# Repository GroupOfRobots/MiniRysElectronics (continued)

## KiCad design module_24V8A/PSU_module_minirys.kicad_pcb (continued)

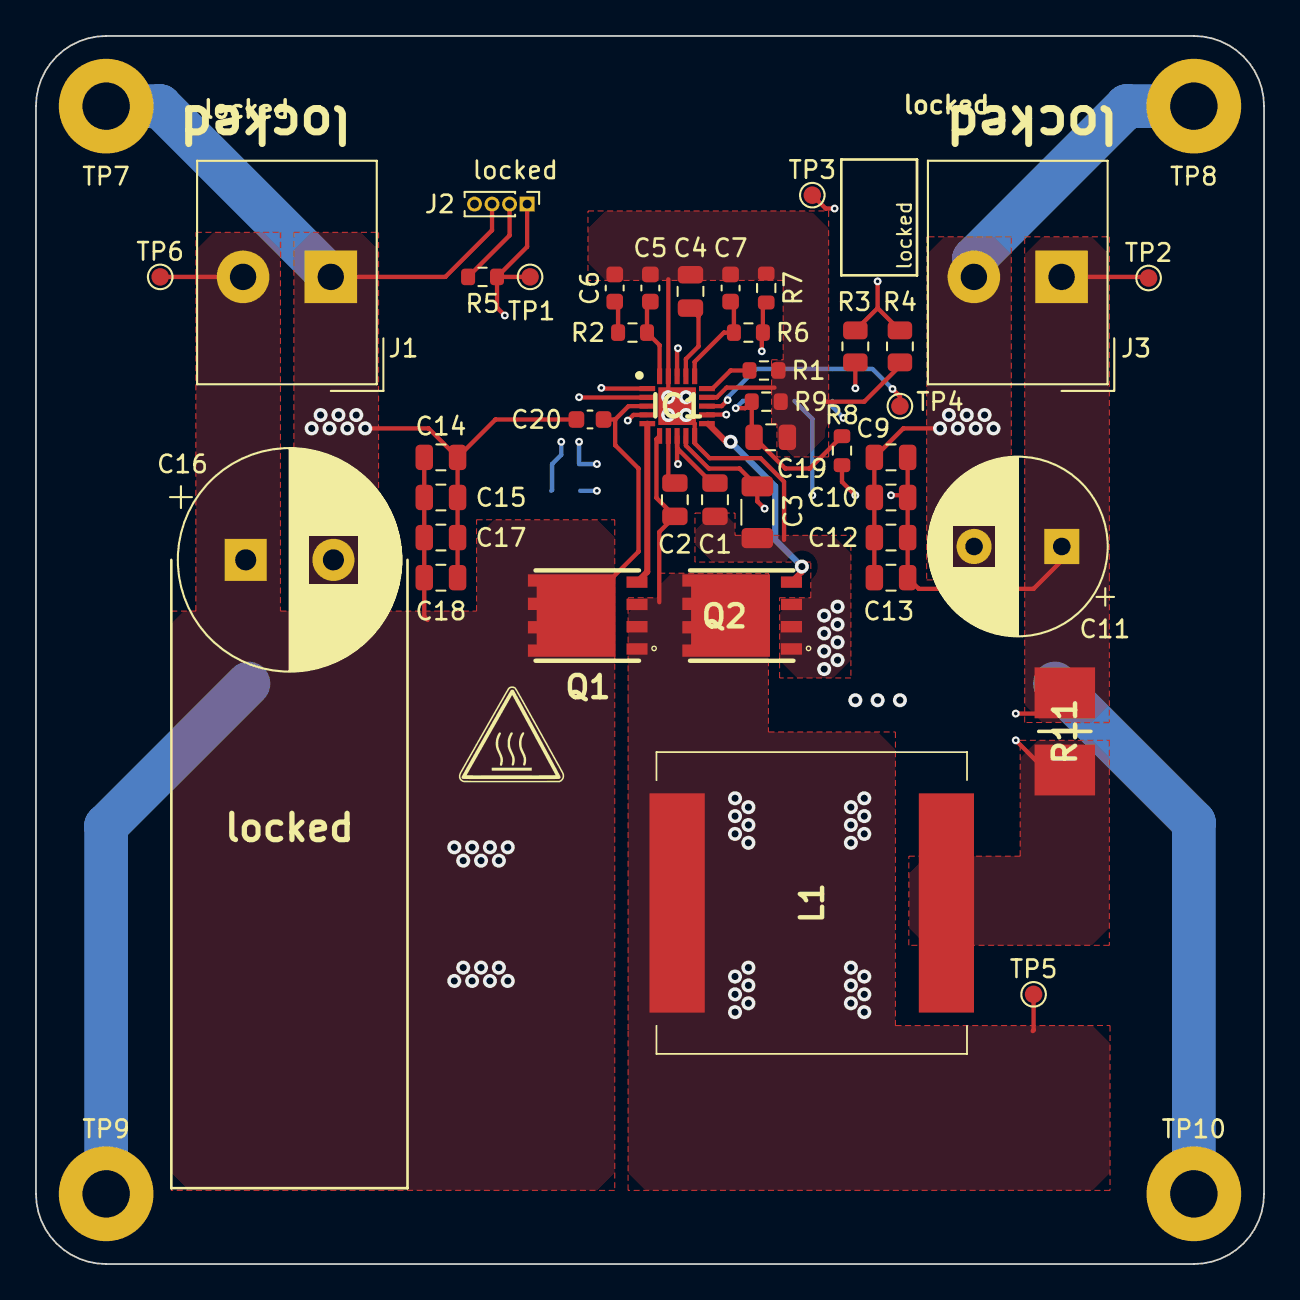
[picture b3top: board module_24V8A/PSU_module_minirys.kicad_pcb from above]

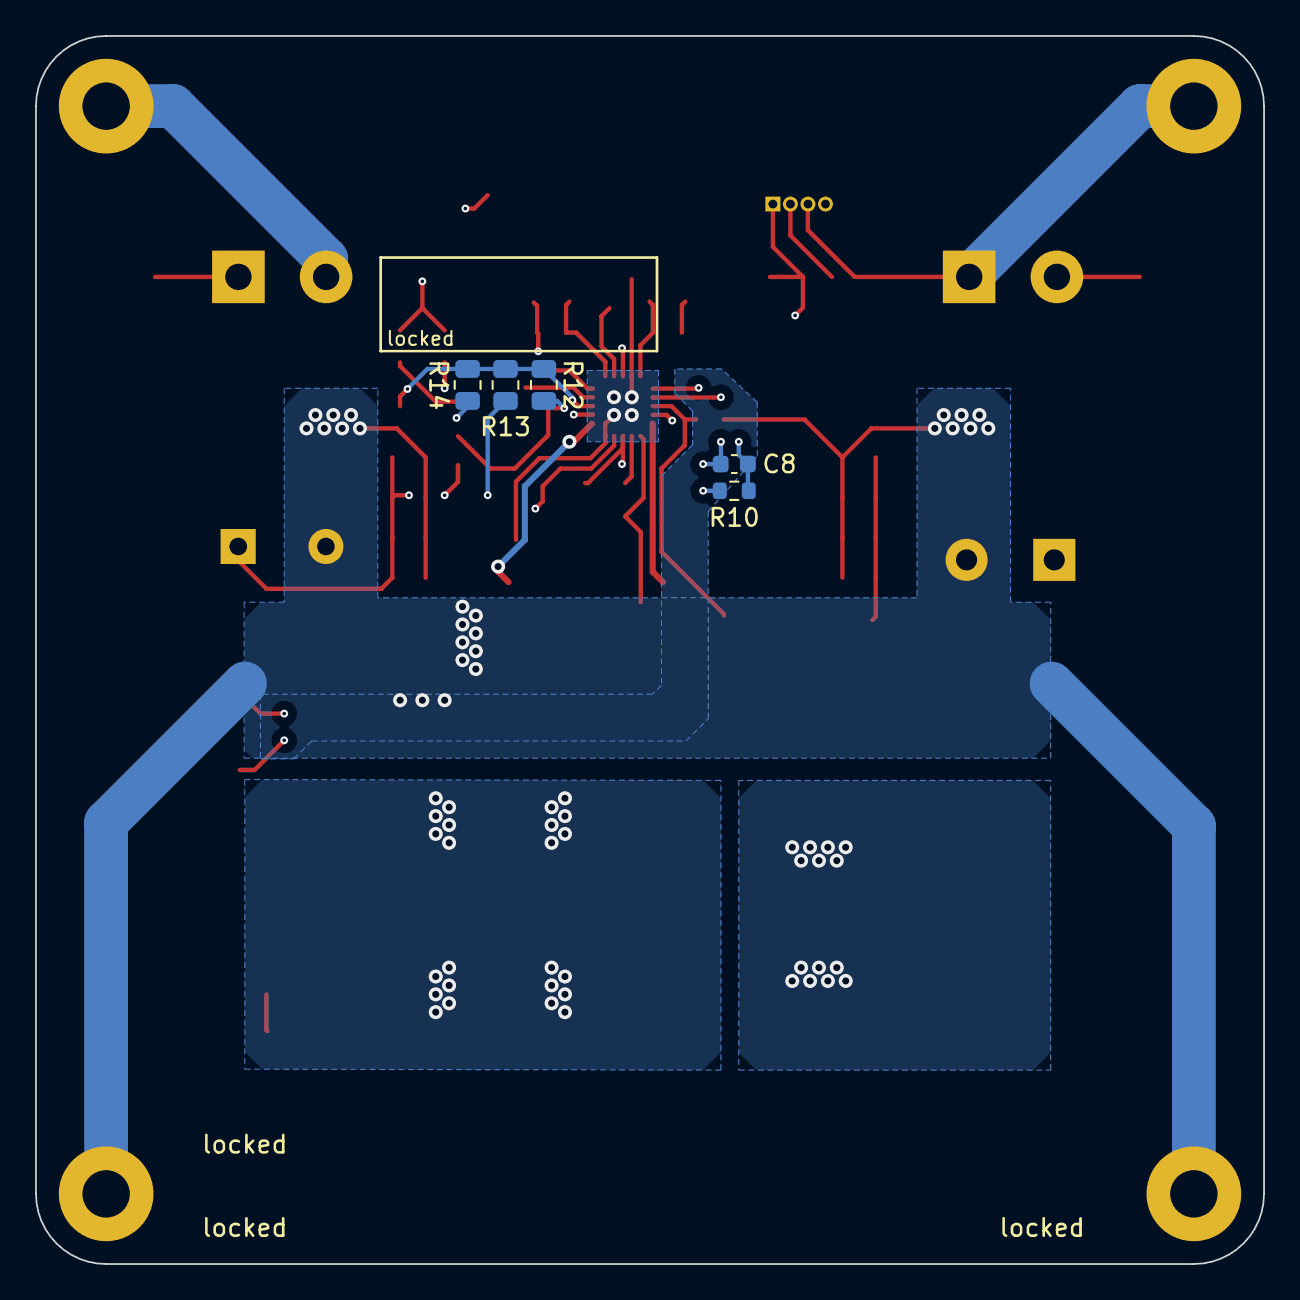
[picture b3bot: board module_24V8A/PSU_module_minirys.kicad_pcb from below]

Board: 4 copper layers, 70.0 x 70.0 mm, 51 parts (5 on the bottom side), 22 nets.

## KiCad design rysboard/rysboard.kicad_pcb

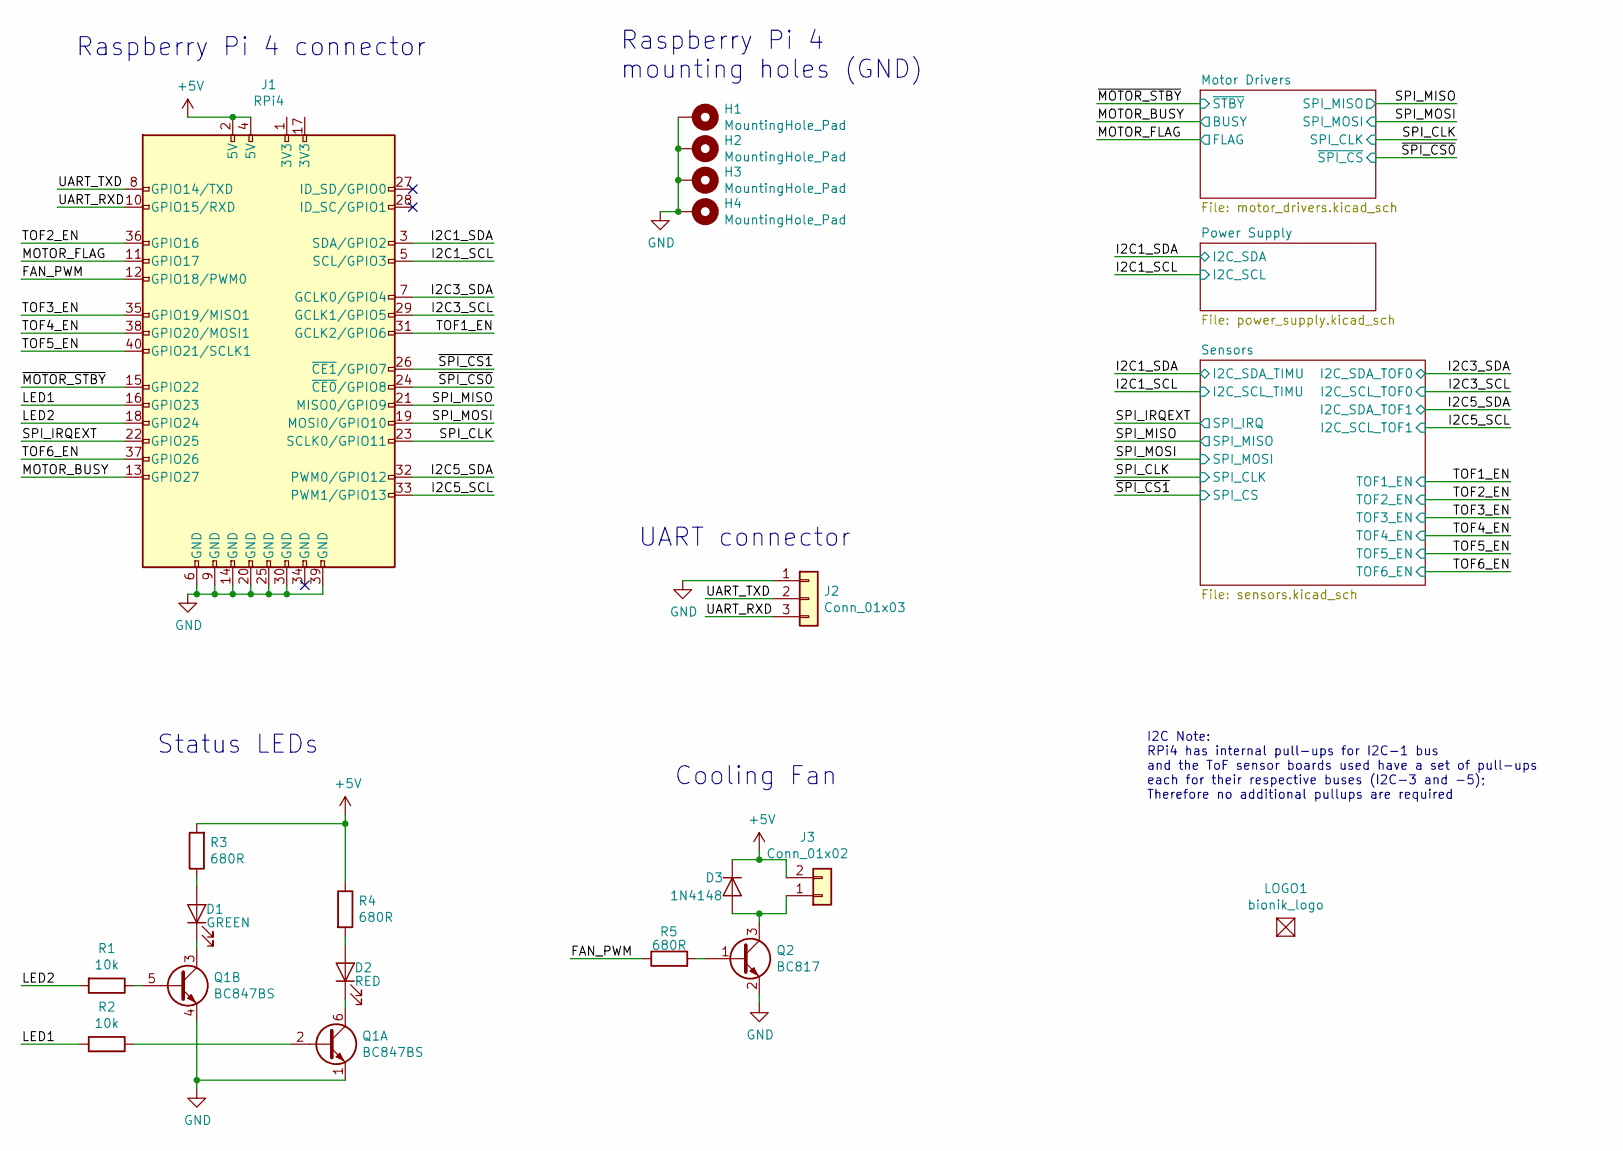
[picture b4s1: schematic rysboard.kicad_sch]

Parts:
D1: GREEN; LED_0805_2012Metric
D2: RED; LED_0805_2012Metric
D3: 1N4148; D_0603_1608Metric
H1, H2, H3, H4: MountingHole_Pad; MountingHole_2.7mm_M2.5_Pad
J1: RPi4; PinSocket_2x20_P2.54mm_Vertical
J2: Conn_01x03; PinHeader_1x03_P2.54mm_Vertical
J3: Conn_01x02; PinHeader_1x02_P2.54mm_Vertical
LOGO1: bionik_logo
Q1: BC847BS; SOT-363_SC-70-6
Q2: BC817; SOT-23
R1, R2: 10k; R_0603_1608Metric
R3, R4, R5: 680R; R_0603_1608Metric

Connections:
+5V: D3.1 (K), J1.2 (5V), J1.4 (5V), J3.2, R3.2, R4.1; also elsewhere on the board
/FAN_PWM: J1.12 (GPIO18/PWM0), R5.1
/I2C1_SCL: J1.5 (SCL/GPIO3); also elsewhere on the board
/I2C1_SDA: J1.3 (SDA/GPIO2); also elsewhere on the board
/I2C3_SCL: J1.29 (GCLK1/GPIO5); also elsewhere on the board
/I2C3_SDA: J1.7 (GCLK0/GPIO4); also elsewhere on the board
/I2C5_SCL: J1.33 (PWM1/GPIO13); also elsewhere on the board
/I2C5_SDA: J1.32 (PWM0/GPIO12); also elsewhere on the board
/LED1: J1.16 (GPIO23), R2.2
/LED2: J1.18 (GPIO24), R1.2
/MOTOR_BUSY: J1.13 (GPIO27); also elsewhere on the board
/MOTOR_FLAG: J1.11 (GPIO17); also elsewhere on the board
/SPI_CLK: J1.23 (SCLK0/GPIO11); also elsewhere on the board
/SPI_IRQEXT: J1.22 (GPIO25); also elsewhere on the board
/SPI_MISO: J1.21 (MISO0/GPIO9); also elsewhere on the board
/SPI_MOSI: J1.19 (MOSI0/GPIO10); also elsewhere on the board
/TOF1_EN: J1.31 (GCLK2/GPIO6); also elsewhere on the board
/TOF2_EN: J1.36 (GPIO16); also elsewhere on the board
/TOF3_EN: J1.35 (GPIO19/MISO1); also elsewhere on the board
/TOF4_EN: J1.38 (GPIO20/MOSI1); also elsewhere on the board
/TOF5_EN: J1.40 (GPIO21/SCLK1); also elsewhere on the board
/TOF6_EN: J1.37 (GPIO26); also elsewhere on the board
/UART_RXD: J1.10 (GPIO15/RXD), J2.3
/UART_TXD: J1.8 (GPIO14/TXD), J2.2
/~MOTOR_STBY: J1.15 (GPIO22); also elsewhere on the board
/~SPI_CS0: J1.24 (~CE0/GPIO8); also elsewhere on the board
/~SPI_CS1: J1.26 (~CE1/GPIO7); also elsewhere on the board
GND: H1.1, H2.1, H3.1, H4.1, J1.6 (GND), J1.9 (GND), J1.14 (GND), J1.20 (GND), J1.25 (GND), J1.30 (GND), J1.39 (GND), J2.1, Q1.1 (E1), Q1.4 (E2), Q2.2 (E); also elsewhere on the board
unnamed: D1.1 (K), Q1.3 (C2)
unnamed: D1.2 (A), R3.1
unnamed: D2.1 (K), Q1.6 (C1)
unnamed: D2.2 (A), R4.2
unnamed: D3.2 (A), J3.1, Q2.3 (C)
unnamed: Q1.2 (B1), R2.1
unnamed: Q1.5 (B2), R1.1
unnamed: Q2.1 (B), R5.2

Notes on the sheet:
Raspberry Pi 4 mounting holes (GND)
Cooling Fan
Status LEDs
I2C Note: RPi4 has internal pull-ups for I2C-1 bus and the ToF sensor boards used have a set of pull-ups each for their respective buses (I2C-3 and -5); Therefore no additional pullups are required
UART connector
Raspberry Pi 4 connector

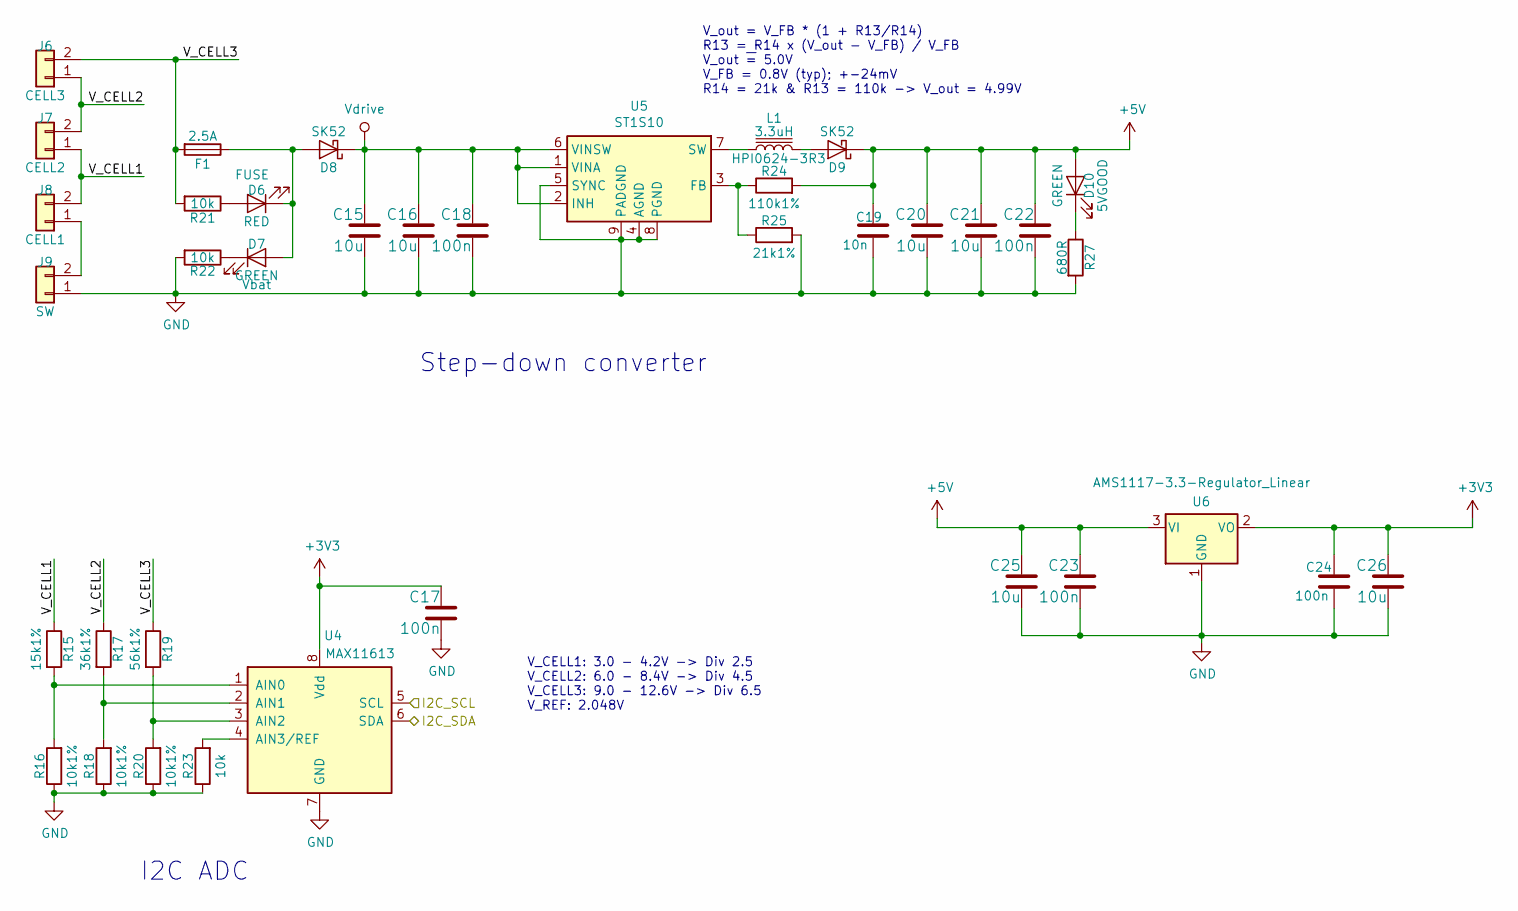
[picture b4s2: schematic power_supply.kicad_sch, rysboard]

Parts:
C15, C16, C20, C21: 10u; C_1206_3216Metric
C17, C18, C22, C23, C24: 100n; C_0603_1608Metric
C19: 10n; C_0603_1608Metric
C25, C26: 10u; C_0603_1608Metric
D6: RED; LED_0805_2012Metric
D7, D10: GREEN; LED_0805_2012Metric
D8, D9: SK52; D_SMB
F1: 2.5A; Fuse_1206_3216Metric
J6: CELL3; Molex_Micro-Fit_3.0_43045-0212_2x01_P3.00mm_Vertical
J7: CELL2; Molex_Micro-Fit_3.0_43045-0212_2x01_P3.00mm_Vertical
J8: CELL1; Molex_Micro-Fit_3.0_43045-0212_2x01_P3.00mm_Vertical
J9: SW; Molex_Micro-Fit_3.0_43045-0212_2x01_P3.00mm_Vertical
L1: 3.3uH; L_6.7x6.7_H2.2
R15: 15k1%; R_0603_1608Metric
R16, R18, R20: 10k1%; R_0603_1608Metric
R17: 36k1%; R_0603_1608Metric
R19: 56k1%; R_0603_1608Metric
R21, R22, R23: 10k; R_0603_1608Metric
R24: 110k1%; R_0603_1608Metric
R25: 21k1%; R_0603_1608Metric
R27: 680R; R_0603_1608Metric
U4: MAX11613; 8-uMAX; PartID MAX11613EUA+
U5: ST1S10; TI_SO-PowerPAD-8; PartID ST1S10PHR
U6: AMS1117-3.3-Regulator_Linear; SOT-223_New

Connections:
+3V3: C17.1, C24.1, C26.1, U4.8 (Vdd), U6.2 (VO); also elsewhere on the board
+5V: C19.1, C20.1, C21.1, C22.1, C23.1, C25.1, D9.1 (K), D10.2 (A), R24.2, U6.3 (VI); also elsewhere on the board
/I2C1_SCL: U4.5 (SCL); also elsewhere on the board
/I2C1_SDA: U4.6 (SDA); also elsewhere on the board
/Power Supply/V_CELL1: J7.1, J8.2, R15.1
/Power Supply/V_CELL2: J6.1, J7.2, R17.1
/Power Supply/V_CELL3: F1.2, J6.2, R19.1, R21.2
GND: C15.2, C16.2, C17.2, C18.2, C19.2, C20.2, C21.2, C22.2, C23.2, C24.2, C25.2, C26.2, J9.1, R16.1, R18.1, R20.1, R22.2, R23.1, R25.2, R27.2, U4.7 (GND), U5.4 (AGND), U5.5 (SYNC), U5.8 (PGND), U5.9 (PADGND), U6.1 (GND); also elsewhere on the board
unnamed: D6.1 (K), D7.2 (A), D8.2 (A), F1.1
unnamed: D6.2 (A), R21.1
unnamed: D7.1 (K), R22.1
unnamed: D9.2 (A), L1.2
unnamed: D10.1 (K), R27.1
unnamed: J8.1, J9.2
unnamed: L1.1, U5.7 (SW)
unnamed: R15.2, R16.2, U4.1 (AIN0)
unnamed: R17.2, R18.2, U4.2 (AIN1)
unnamed: R19.2, R20.2, U4.3 (AIN2)
unnamed: R23.2, U4.4 (AIN3/REF)
unnamed: R24.1, R25.1, U5.3 (FB)
Vdrive: C15.1, C16.1, C18.1, D8.1 (K), U5.1 (VINA), U5.2 (INH), U5.6 (VINSW); also elsewhere on the board

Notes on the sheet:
Step-down converter
V_out = V_FB * (1 + R13/R14) R13 = R14 x (V_out - V_FB) / V_FB V_out ~{=} 5.0V V_FB = 0.8V (typ); +-24mV R14 = 21k & R13 = 110k -> V_out = 4.99V
V_CELL1: 3.0 - 4.2V -> Div 2.5 V_CELL2: 6.0 - 8.4V -> Div 4.5 V_CELL3: 9.0 - 12.6V -> Div 6.5 V_REF: 2.048V
I2C ADC

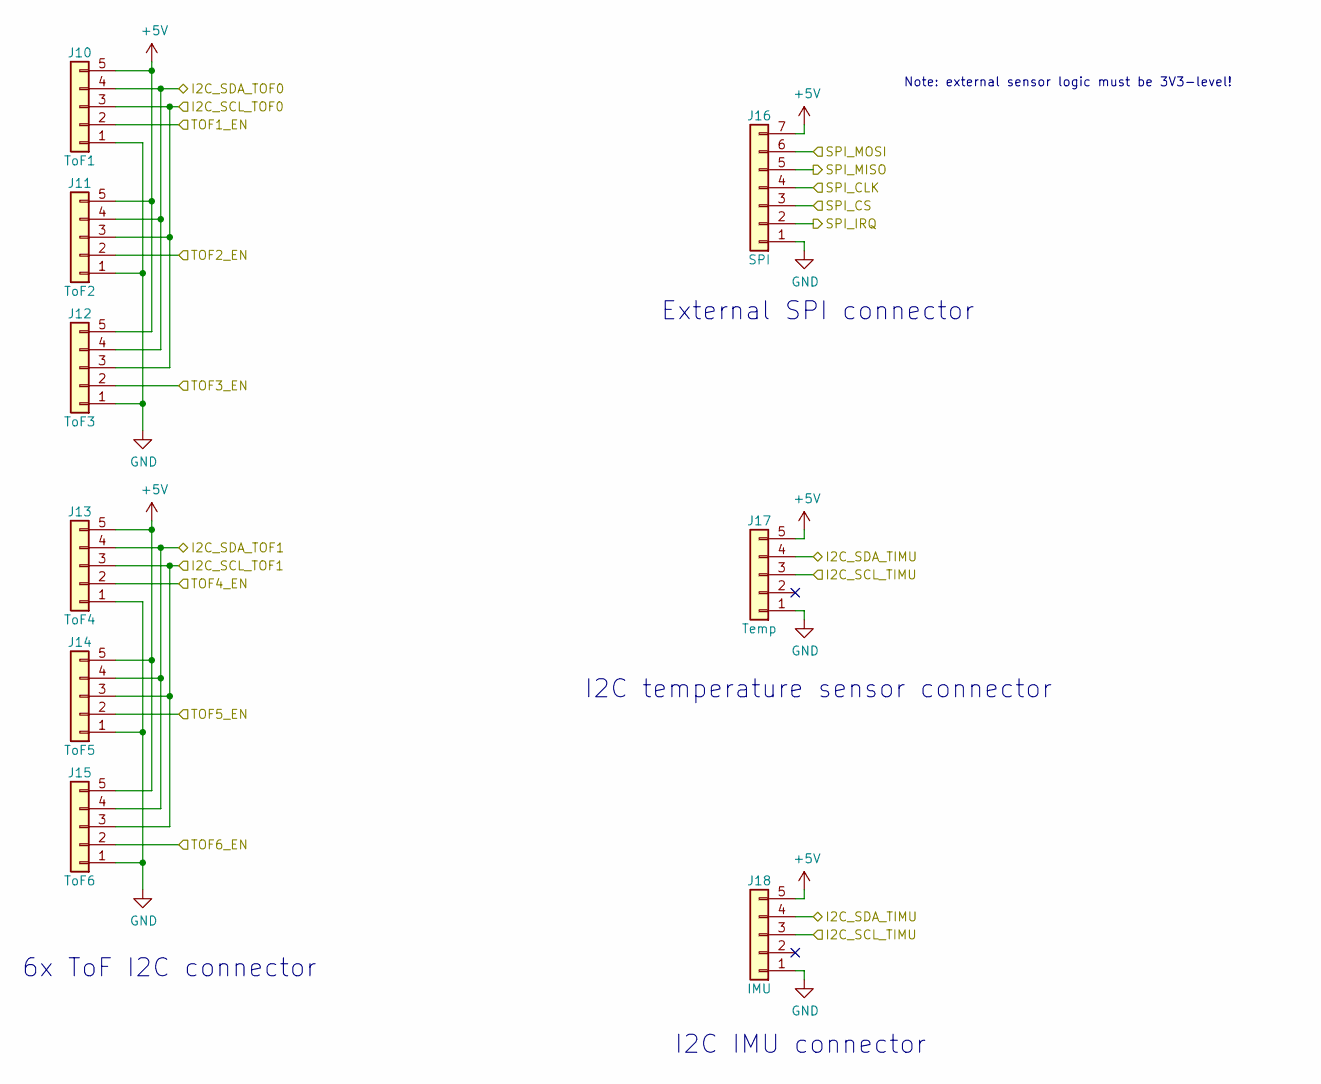
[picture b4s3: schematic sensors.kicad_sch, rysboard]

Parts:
J10: ToF1; Molex_PicoBlade_53047-0510_1x05_P1.25mm_Vertical
J11: ToF2; Molex_PicoBlade_53047-0510_1x05_P1.25mm_Vertical
J12: ToF3; Molex_PicoBlade_53047-0510_1x05_P1.25mm_Vertical
J13: ToF4; Molex_PicoBlade_53047-0510_1x05_P1.25mm_Vertical
J14: ToF5; Molex_PicoBlade_53047-0510_1x05_P1.25mm_Vertical
J15: ToF6; Molex_PicoBlade_53047-0510_1x05_P1.25mm_Vertical
J16: SPI; Molex_PicoBlade_53047-0710_1x07_P1.25mm_Vertical
J17: Temp; Molex_PicoBlade_53047-0510_1x05_P1.25mm_Vertical
J18: IMU; Molex_PicoBlade_53047-0510_1x05_P1.25mm_Vertical

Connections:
+5V: J10.5, J11.5, J12.5, J13.5, J14.5, J15.5, J16.7, J17.5, J18.5; also elsewhere on the board
/I2C1_SCL: J17.3, J18.3; also elsewhere on the board
/I2C1_SDA: J17.4, J18.4; also elsewhere on the board
/I2C3_SCL: J10.3, J11.3, J12.3; also elsewhere on the board
/I2C3_SDA: J10.4, J11.4, J12.4; also elsewhere on the board
/I2C5_SCL: J13.3, J14.3, J15.3; also elsewhere on the board
/I2C5_SDA: J13.4, J14.4, J15.4; also elsewhere on the board
/SPI_CLK: J16.4; also elsewhere on the board
/SPI_IRQEXT: J16.2; also elsewhere on the board
/SPI_MISO: J16.5; also elsewhere on the board
/SPI_MOSI: J16.6; also elsewhere on the board
/TOF1_EN: J10.2; also elsewhere on the board
/TOF2_EN: J11.2; also elsewhere on the board
/TOF3_EN: J12.2; also elsewhere on the board
/TOF4_EN: J13.2; also elsewhere on the board
/TOF5_EN: J14.2; also elsewhere on the board
/TOF6_EN: J15.2; also elsewhere on the board
/~SPI_CS1: J16.3; also elsewhere on the board
GND: J10.1, J11.1, J12.1, J13.1, J14.1, J15.1, J16.1, J17.1, J18.1; also elsewhere on the board

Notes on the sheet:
Note: external sensor logic must be 3V3-level!
External SPI connector
I2C temperature sensor connector
I2C IMU connector
6x ToF I2C connector

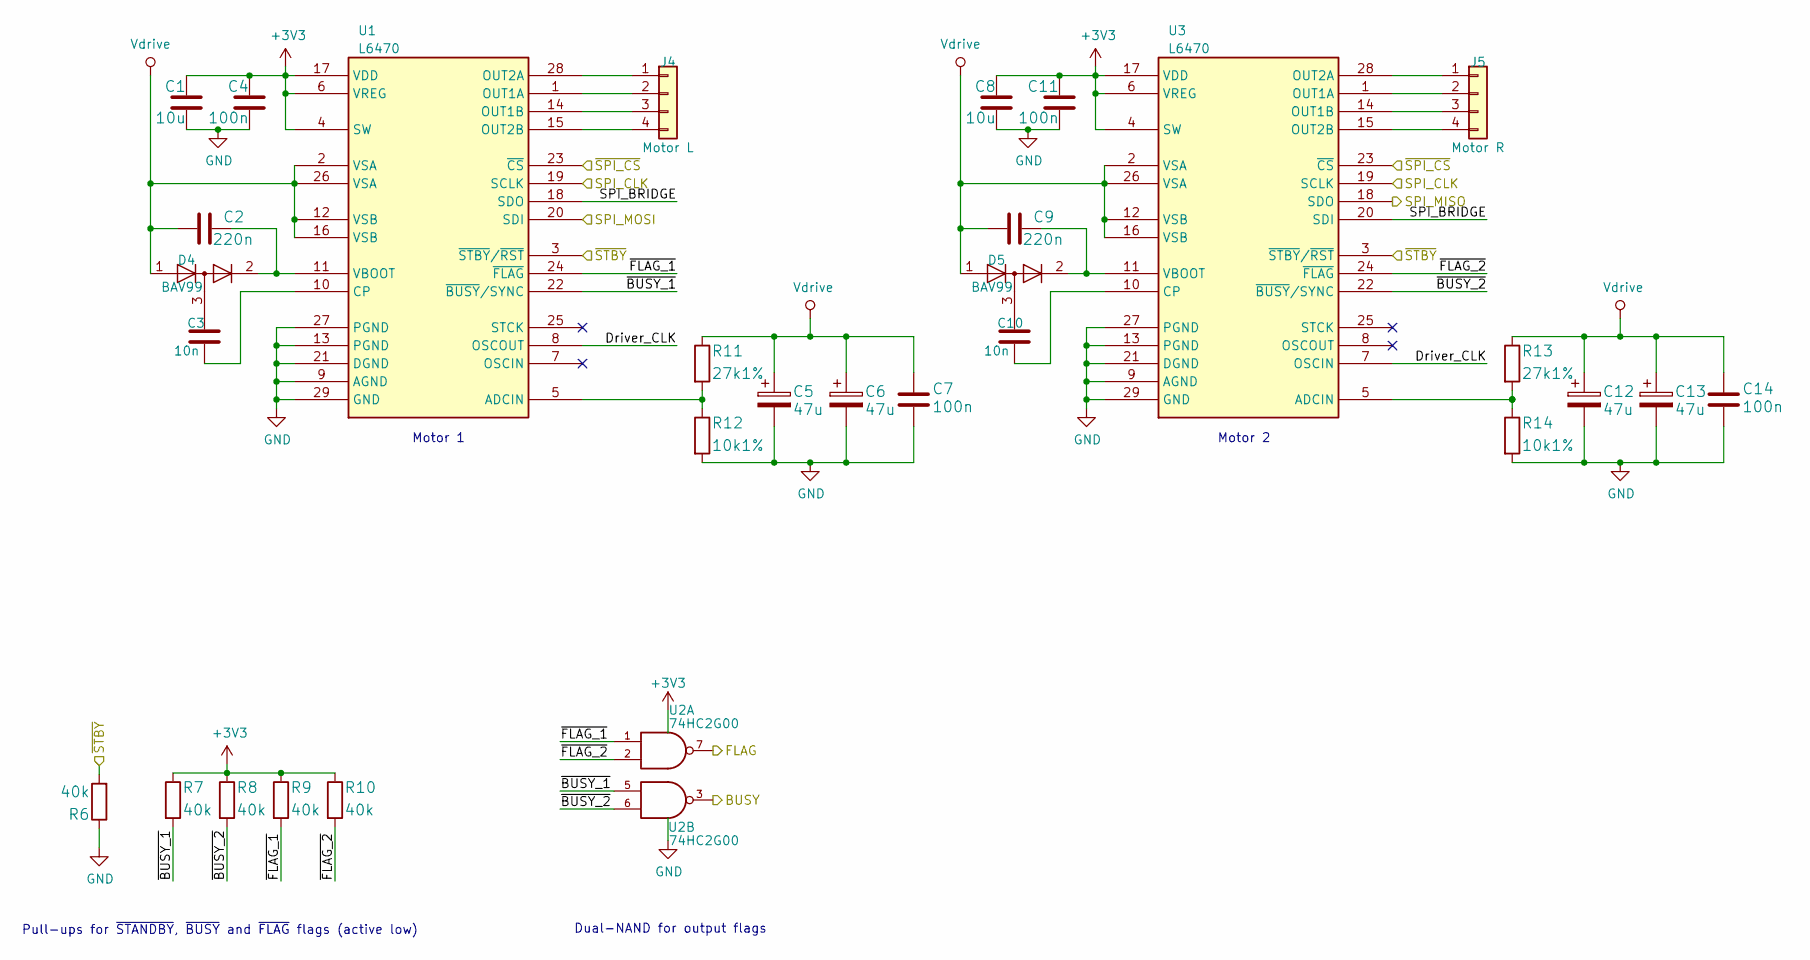
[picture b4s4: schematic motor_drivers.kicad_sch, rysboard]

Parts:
C1, C8: 10u; C_1206_3216Metric
C2, C9: 220n; C_0805_2012Metric
C3, C10: 10n; C_0603_1608Metric
C4, C7, C11, C14: 100n; C_0603_1608Metric
C5, C6, C12, C13: 47u; CP_EIA-7343-31_Kemet-D
D4, D5: BAV99; SOT-23
J4: Motor L; Molex_Micro-Fit_3.0_43650-0415_1x04_P3.00mm_Vertical
J5: Motor R; Molex_Micro-Fit_3.0_43650-0415_1x04_P3.00mm_Vertical
R6, R7, R8, R9, R10: 40k; R_0603_1608Metric
R11, R13: 27k1%; R_0603_1608Metric
R12, R14: 10k1%; R_0603_1608Metric
U1, U3: L6470; HTSSOP-28-1EP_4.4x9.7mm_P0.65mm_EP3.4x9.5mm_ThermalVias; PartID L6470H
U2: 74HC2G00; TSSOP-8_3x3mm_P0.65mm

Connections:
+3V3: C1.1, C4.1, C8.1, C11.1, R7.1, R8.1, R9.1, R10.1, U1.4 (SW), U1.6 (VREG), U1.17 (VDD), U2.8 (VCC), U3.4 (SW), U3.6 (VREG), U3.17 (VDD); also elsewhere on the board
/MOTOR_BUSY: U2.3; also elsewhere on the board
/MOTOR_FLAG: U2.7; also elsewhere on the board
/Motor Drivers/Driver_CLK: U1.8 (OSCOUT), U3.7 (OSCIN)
/Motor Drivers/SPI_BRIDGE: U1.18 (SDO), U3.20 (SDI)
/Motor Drivers/~BUSY_1: R7.2, U1.22 (~BUSY/SYNC), U2.5
/Motor Drivers/~BUSY_2: R8.2, U2.6, U3.22 (~BUSY/SYNC)
/Motor Drivers/~FLAG_1: R9.2, U1.24 (~FLAG), U2.1
/Motor Drivers/~FLAG_2: R10.2, U2.2, U3.24 (~FLAG)
/SPI_CLK: U1.19 (SCLK), U3.19 (SCLK); also elsewhere on the board
/SPI_MISO: U3.18 (SDO); also elsewhere on the board
/SPI_MOSI: U1.20 (SDI); also elsewhere on the board
/~MOTOR_STBY: R6.2, U1.3 (~STBY/~RST), U3.3 (~STBY/~RST); also elsewhere on the board
/~SPI_CS0: U1.23 (~CS), U3.23 (~CS); also elsewhere on the board
GND: C1.2, C4.2, C5.2, C6.2, C7.2, C8.2, C11.2, C12.2, C13.2, C14.2, R6.1, R12.2, R14.2, U1.9 (AGND), U1.13 (PGND), U1.21 (DGND), U1.27 (PGND), U1.29 (GND), U2.4 (GND), U3.9 (AGND), U3.13 (PGND), U3.21 (DGND), U3.27 (PGND), U3.29 (GND); also elsewhere on the board
unnamed: C2.2, D4.2 (A), U1.11 (VBOOT)
unnamed: C3.1, D4.3 (K)
unnamed: C3.2, U1.10 (CP)
unnamed: C9.2, D5.2 (A), U3.11 (VBOOT)
unnamed: C10.1, D5.3 (K)
unnamed: C10.2, U3.10 (CP)
unnamed: J4.1, U1.28 (OUT2A)
unnamed: J4.2, U1.1 (OUT1A)
unnamed: J4.3, U1.14 (OUT1B)
unnamed: J4.4, U1.15 (OUT2B)
unnamed: J5.1, U3.28 (OUT2A)
unnamed: J5.2, U3.1 (OUT1A)
unnamed: J5.3, U3.14 (OUT1B)
unnamed: J5.4, U3.15 (OUT2B)
unnamed: R11.2, R12.1, U1.5 (ADCIN)
unnamed: R13.2, R14.1, U3.5 (ADCIN)
Vdrive: C2.1, C5.1, C6.1, C7.1, C9.1, C12.1, C13.1, C14.1, D4.1 (K), D5.1 (K), R11.1, R13.1, U1.2 (VSA), U1.12 (VSB), U1.16 (VSB), U1.26 (VSA), U3.2 (VSA), U3.12 (VSB), U3.16 (VSB), U3.26 (VSA); also elsewhere on the board

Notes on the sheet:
Motor 1
Motor 2
Pull-ups for ~{STANDBY}, ~{BUSY} and ~{FLAG} flags (active low)
Dual-NAND for output flags

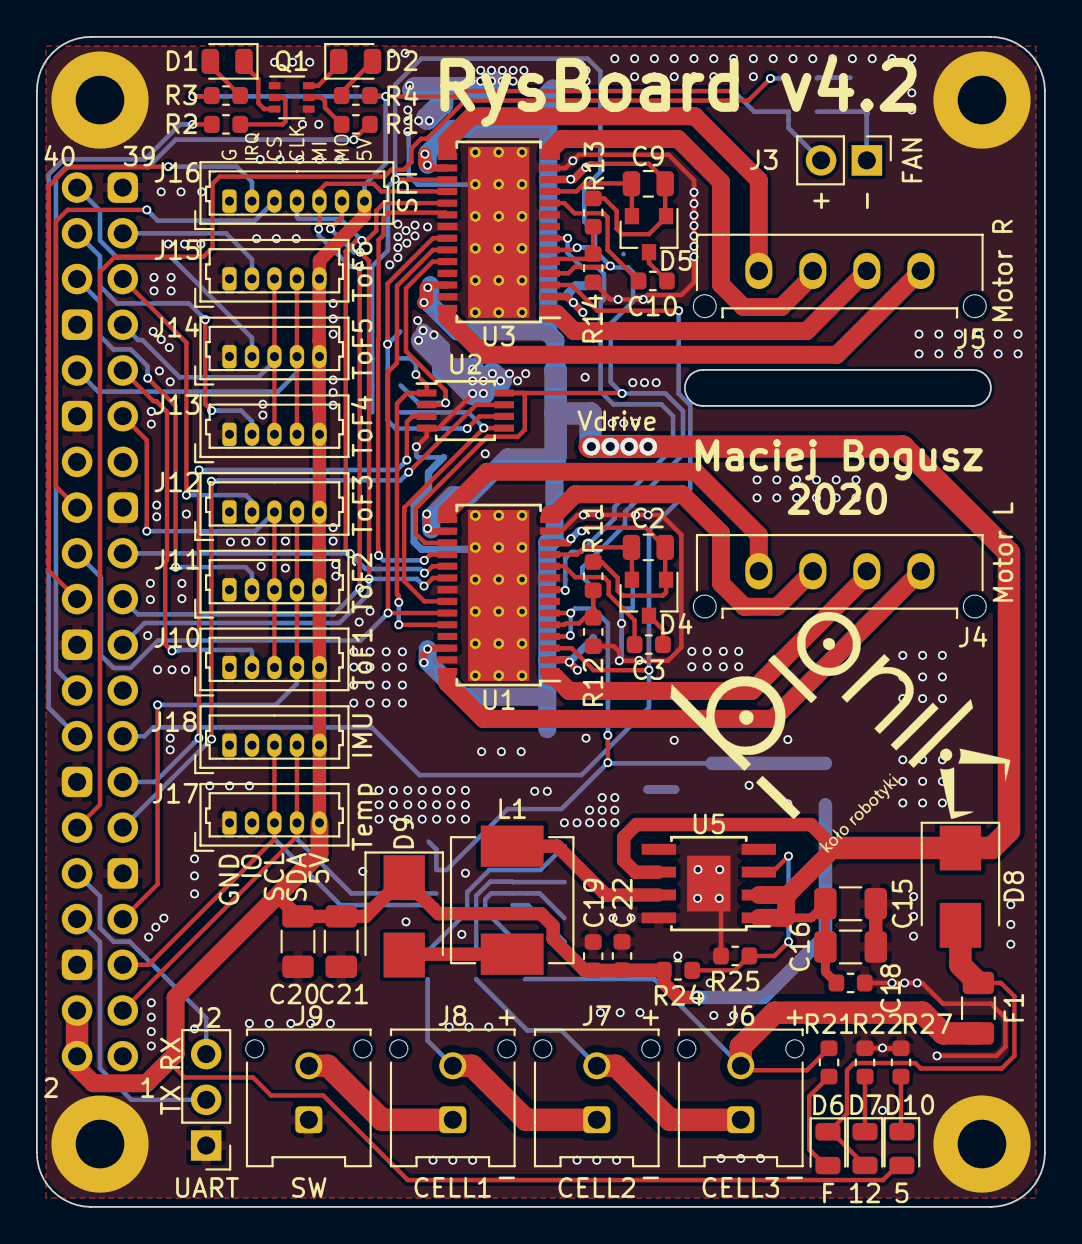
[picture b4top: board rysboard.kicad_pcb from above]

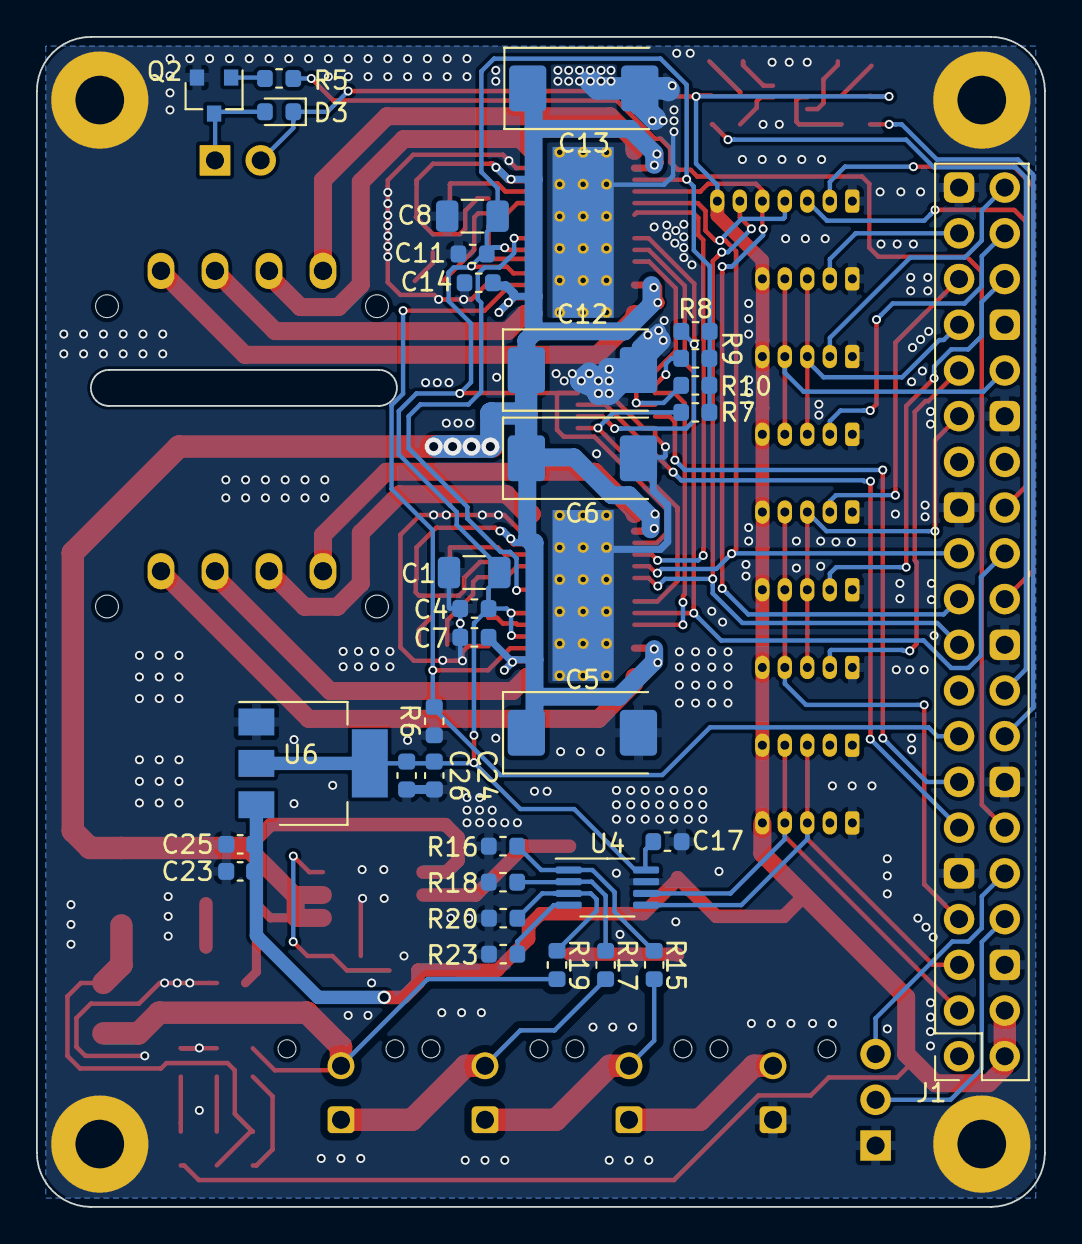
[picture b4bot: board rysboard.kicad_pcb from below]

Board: 2 copper layers, 56.0 x 65.0 mm, 95 parts (33 on the bottom side), 75 nets.

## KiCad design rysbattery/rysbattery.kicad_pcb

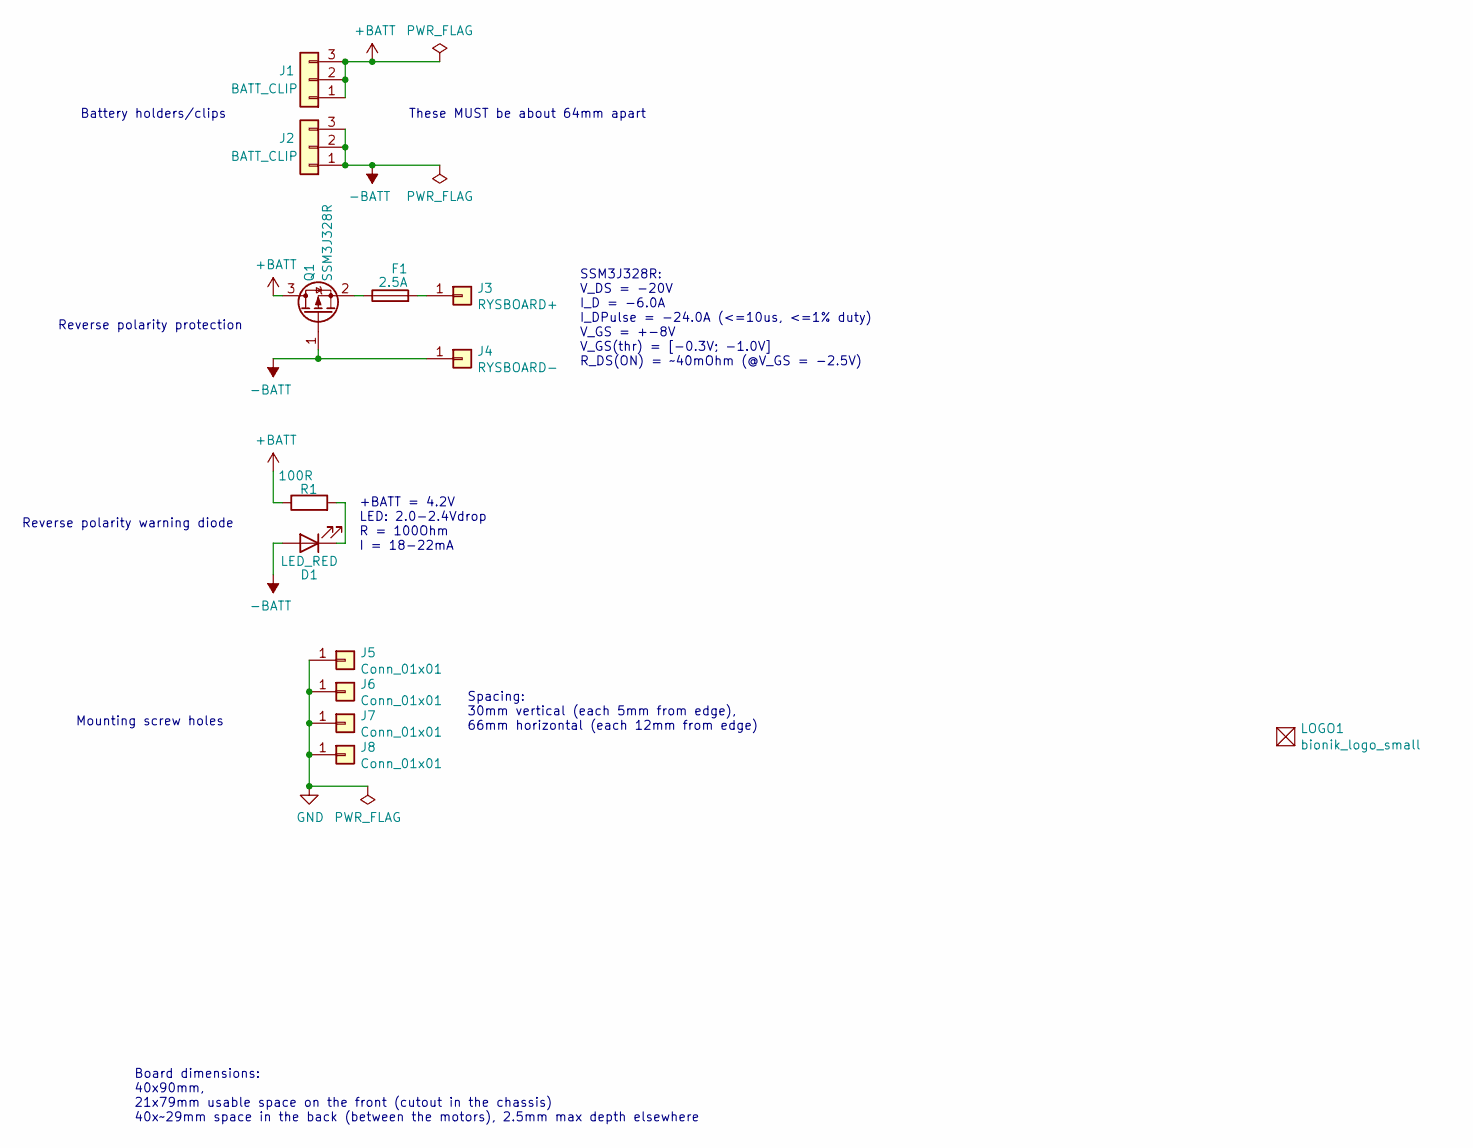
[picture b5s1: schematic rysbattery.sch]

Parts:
D1: LED_RED; LED_0805_2012Metric_Pad1.15x1.40mm_HandSolder
F1: 2.5A; Fuse_1206_3216Metric_Pad1.42x1.75mm_HandSolder
J1, J2: BATT_CLIP; keystone_54
J3: RYSBOARD+; SolderWire-0.75sqmm_1x01_D1.25mm_OD2.3mm_Relief
J4: RYSBOARD-; SolderWire-0.75sqmm_1x01_D1.25mm_OD2.3mm_Relief
J5, J6, J7, J8: Conn_01x01; MountingHole_3.2mm_M3_DIN965_Pad
LOGO1: bionik_logo_small
Q1: SSM3J328R; SOT-23_Handsoldering
R1: 100R; R_0603_1608Metric_Pad1.05x0.95mm_HandSolder

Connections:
+BATT: J1.1, J1.2, J1.3, Q1.3 (D), R1.1
-BATT: D1.2 (A), J2.1, J2.2, J2.3, J4.1, Q1.1 (G)
GND: J5.1, J6.1, J7.1, J8.1
unnamed: D1.1 (K), R1.2
unnamed: F1.1, Q1.2 (S)
unnamed: F1.2, J3.1

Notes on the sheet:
Reverse polarity warning diode
+BATT = 4.2V LED: 2.0-2.4Vdrop R = 100Ohm I = 18-22mA
Battery holders/clips
These MUST be about 64mm apart
Reverse polarity protection
Mounting screw holes
SSM3J328R: V_DS = -20V I_D = -6.0A I_DPulse = -24.0A (<=10us, <=1% duty) V_GS = +-8V V_GS(thr) = [-0.3V; -1.0V] R_DS(ON) = ~~40mOhm (@V_GS = -2.5V)
Spacing: 30mm vertical (each 5mm from edge), 66mm horizontal (each 12mm from edge)
Board dimensions: 40x90mm, 21x79mm usable space on the front (cutout in the chassis) 40x~~29mm space in the back (between the motors), 2.5mm max depth elsewhere

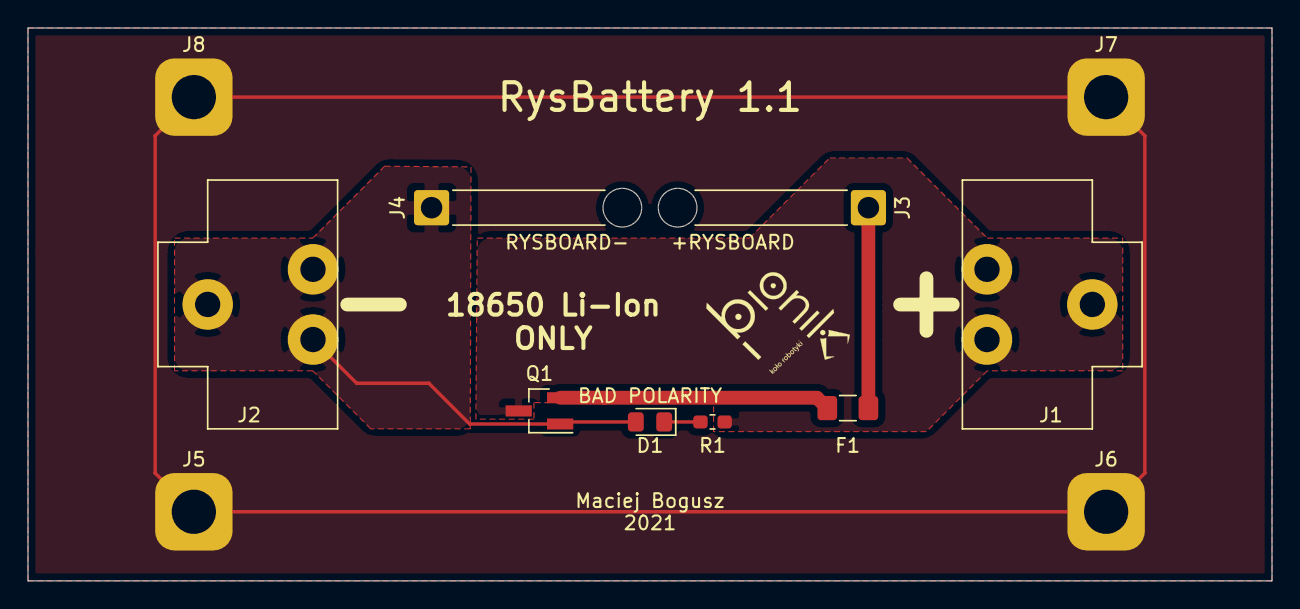
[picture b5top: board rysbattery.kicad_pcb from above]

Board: 2 copper layers, 90.0 x 40.0 mm, 13 parts (0 on the bottom side), 6 nets.
